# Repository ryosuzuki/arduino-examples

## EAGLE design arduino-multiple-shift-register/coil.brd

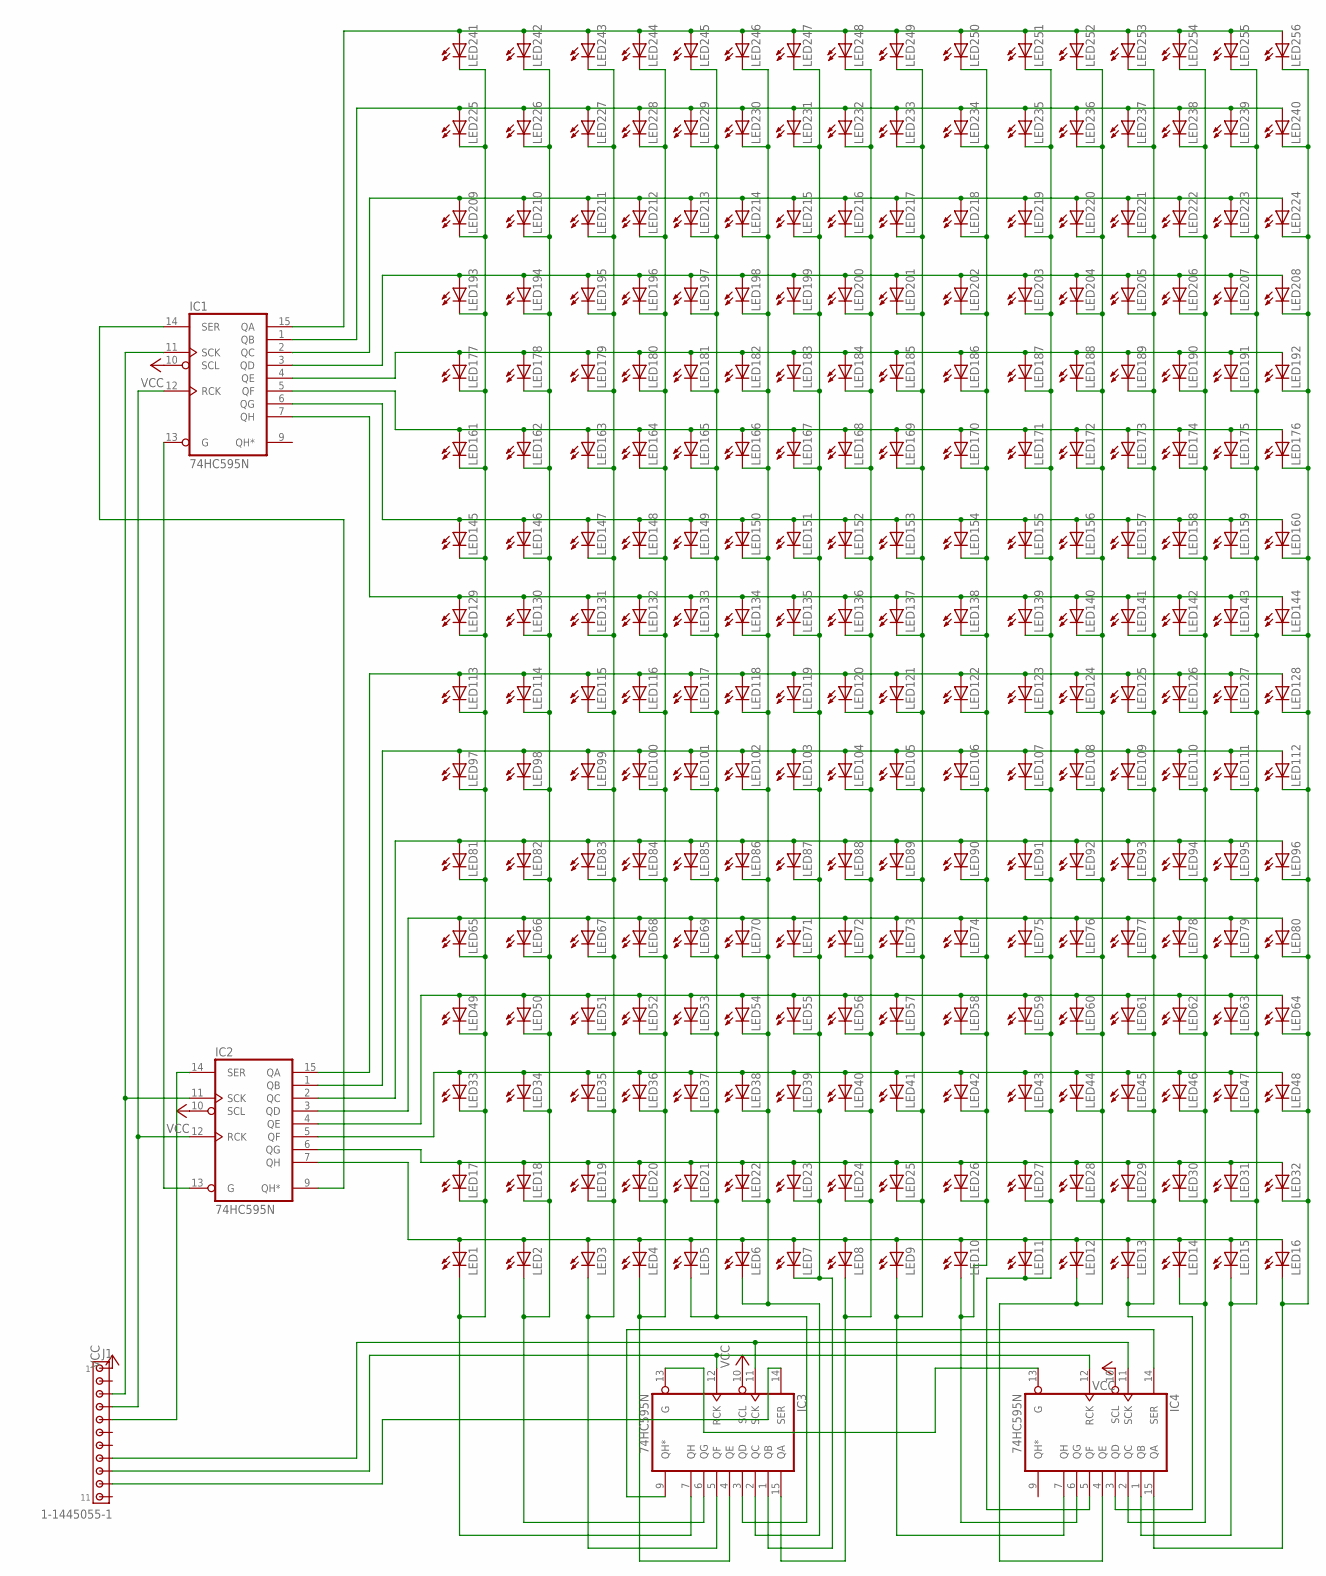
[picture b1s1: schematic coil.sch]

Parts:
IC1, IC2, IC3, IC4: 74HC595N; DIL16
J1: 1-1445055-1
LED1, LED2, LED3, LED4, LED5, LED6, LED7, LED8, LED9, LED10, LED11, LED12, LED13, LED14, LED15, LED16, LED17, LED18, LED19, LED20, LED21, LED22, LED23, LED24, LED25, LED26, LED27, LED28, LED29, LED30, LED31, LED32, LED33, LED34, LED35, LED36, LED37, LED38, LED39, LED40, LED41, LED42, LED43, LED44, LED45, LED46, LED47, LED48, LED49, LED50, LED51, LED52, LED53, LED54, LED55, LED56, LED57, LED58, LED59, LED60, LED61, LED62, LED63, LED64, LED65, LED66, LED67, LED68, LED69, LED70, LED71, LED72, LED73, LED74, LED75, LED76, LED77, LED78, LED79, LED80, LED81, LED82, LED83, LED84, LED85, LED86, LED87, LED88, LED89, LED90, LED91, LED92, LED93, LED94, LED95, LED96, LED97, LED98, LED99, LED100, LED101, LED102, LED103, LED104, LED105, LED106, LED107, LED108, LED109, LED110, LED111, LED112, LED113, LED114, LED115, LED116, LED117, LED118, LED119, LED120, LED121, LED122, LED123, LED124, LED125, LED126, LED127, LED128, LED129, LED130, LED131, LED132, LED133, LED134, LED135, LED136, LED137, LED138, LED139, LED140, LED141, LED142, LED143, LED144, LED145, LED146, LED147, LED148, LED149, LED150, LED151, LED152, LED153, LED154, LED155, LED156, LED157, LED158, LED159, LED160, LED161, LED162, LED163, LED164, LED165, LED166, LED167, LED168, LED169, LED170, LED171, LED172, LED173, LED174, LED175, LED176, LED177, LED178, LED179, LED180, LED181, LED182, LED183, LED184, LED185, LED186, LED187, LED188, LED189, LED190, LED191, LED192, LED193, LED194, LED195, LED196, LED197, LED198, LED199, LED200, LED201, LED202, LED203, LED204, LED205, LED206, LED207, LED208, LED209, LED210, LED211, LED212, LED213, LED214, LED215, LED216, LED217, LED218, LED219, LED220, LED221, LED222, LED223, LED224, LED225, LED226, LED227, LED228, LED229, LED230, LED231, LED232, LED233, LED234, LED235, LED236, LED237, LED238, LED239, LED240, LED241, LED242, LED243, LED244, LED245, LED246, LED247, LED248, LED249, LED250, LED251, LED252, LED253, LED254, LED255, LED256: LED5MM

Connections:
GND: IC1.8 (GND), IC2.8 (GND), IC3.8 (GND), IC4.8 (GND)
unnamed: IC2.7 (QH), LED1.A, LED2.A, LED3.A, LED4.A, LED5.A, LED6.A, LED7.A, LED8.A, LED9.A, LED10.A, LED11.A, LED12.A, LED13.A, LED14.A, LED15.A, LED16.A
unnamed: IC2.6 (QG), LED17.A, LED18.A, LED19.A, LED20.A, LED21.A, LED22.A, LED23.A, LED24.A, LED25.A, LED26.A, LED27.A, LED28.A, LED29.A, LED30.A, LED31.A, LED32.A
unnamed: IC2.5 (QF), LED33.A, LED34.A, LED35.A, LED36.A, LED37.A, LED38.A, LED39.A, LED40.A, LED41.A, LED42.A, LED43.A, LED44.A, LED45.A, LED46.A, LED47.A, LED48.A
unnamed: IC2.4 (QE), LED49.A, LED50.A, LED51.A, LED52.A, LED53.A, LED54.A, LED55.A, LED56.A, LED57.A, LED58.A, LED59.A, LED60.A, LED61.A, LED62.A, LED63.A, LED64.A
unnamed: IC2.3 (QD), LED65.A, LED66.A, LED67.A, LED68.A, LED69.A, LED70.A, LED71.A, LED72.A, LED73.A, LED74.A, LED75.A, LED76.A, LED77.A, LED78.A, LED79.A, LED80.A
unnamed: IC2.2 (QC), LED81.A, LED82.A, LED83.A, LED84.A, LED85.A, LED86.A, LED87.A, LED88.A, LED89.A, LED90.A, LED91.A, LED92.A, LED93.A, LED94.A, LED95.A, LED96.A
unnamed: IC2.1 (QB), LED97.A, LED98.A, LED99.A, LED100.A, LED101.A, LED102.A, LED103.A, LED104.A, LED105.A, LED106.A, LED107.A, LED108.A, LED109.A, LED110.A, LED111.A, LED112.A
unnamed: IC2.15 (QA), LED113.A, LED114.A, LED115.A, LED116.A, LED117.A, LED118.A, LED119.A, LED120.A, LED121.A, LED122.A, LED123.A, LED124.A, LED125.A, LED126.A, LED127.A, LED128.A
unnamed: IC1.7 (QH), LED129.A, LED130.A, LED131.A, LED132.A, LED133.A, LED134.A, LED135.A, LED136.A, LED137.A, LED138.A, LED139.A, LED140.A, LED141.A, LED142.A, LED143.A, LED144.A
unnamed: IC1.6 (QG), LED145.A, LED146.A, LED147.A, LED148.A, LED149.A, LED150.A, LED151.A, LED152.A, LED153.A, LED154.A, LED155.A, LED156.A, LED157.A, LED158.A, LED159.A, LED160.A
unnamed: IC1.5 (QF), LED161.A, LED162.A, LED163.A, LED164.A, LED165.A, LED166.A, LED167.A, LED168.A, LED169.A, LED170.A, LED171.A, LED172.A, LED173.A, LED174.A, LED175.A, LED176.A
unnamed: IC1.4 (QE), LED177.A, LED178.A, LED179.A, LED180.A, LED181.A, LED182.A, LED183.A, LED184.A, LED185.A, LED186.A, LED187.A, LED188.A, LED189.A, LED190.A, LED191.A, LED192.A
unnamed: IC1.3 (QD), LED193.A, LED194.A, LED195.A, LED196.A, LED197.A, LED198.A, LED199.A, LED200.A, LED201.A, LED202.A, LED203.A, LED204.A, LED205.A, LED206.A, LED207.A, LED208.A
unnamed: IC1.2 (QC), LED209.A, LED210.A, LED211.A, LED212.A, LED213.A, LED214.A, LED215.A, LED216.A, LED217.A, LED218.A, LED219.A, LED220.A, LED221.A, LED222.A, LED223.A, LED224.A
unnamed: IC1.1 (QB), LED225.A, LED226.A, LED227.A, LED228.A, LED229.A, LED230.A, LED231.A, LED232.A, LED233.A, LED234.A, LED235.A, LED236.A, LED237.A, LED238.A, LED239.A, LED240.A
unnamed: IC1.15 (QA), LED241.A, LED242.A, LED243.A, LED244.A, LED245.A, LED246.A, LED247.A, LED248.A, LED249.A, LED250.A, LED251.A, LED252.A, LED253.A, LED254.A, LED255.A, LED256.A
unnamed: IC4.3 (QD), LED13.K (C), LED29.K (C), LED45.K (C), LED61.K (C), LED77.K (C), LED93.K (C), LED109.K (C), LED125.K (C), LED141.K (C), LED157.K (C), LED173.K (C), LED189.K (C), LED205.K (C), LED221.K (C), LED237.K (C), LED253.K (C)
unnamed: IC4.2 (QC), LED14.K (C), LED30.K (C), LED46.K (C), LED62.K (C), LED78.K (C), LED94.K (C), LED110.K (C), LED126.K (C), LED142.K (C), LED158.K (C), LED174.K (C), LED190.K (C), LED206.K (C), LED222.K (C), LED238.K (C), LED254.K (C)
unnamed: IC4.1 (QB), LED15.K (C), LED31.K (C), LED47.K (C), LED63.K (C), LED79.K (C), LED95.K (C), LED111.K (C), LED127.K (C), LED143.K (C), LED159.K (C), LED175.K (C), LED191.K (C), LED207.K (C), LED223.K (C), LED239.K (C), LED255.K (C)
unnamed: IC3.7 (QH), LED1.K (C), LED17.K (C), LED33.K (C), LED49.K (C), LED65.K (C), LED81.K (C), LED97.K (C), LED113.K (C), LED129.K (C), LED145.K (C), LED161.K (C), LED177.K (C), LED193.K (C), LED209.K (C), LED225.K (C), LED241.K (C)
unnamed: IC3.6 (QG), LED2.K (C), LED18.K (C), LED34.K (C), LED50.K (C), LED66.K (C), LED82.K (C), LED98.K (C), LED114.K (C), LED130.K (C), LED146.K (C), LED162.K (C), LED178.K (C), LED194.K (C), LED210.K (C), LED226.K (C), LED242.K (C)
unnamed: IC3.5 (QF), LED3.K (C), LED19.K (C), LED35.K (C), LED51.K (C), LED67.K (C), LED83.K (C), LED99.K (C), LED115.K (C), LED131.K (C), LED147.K (C), LED163.K (C), LED179.K (C), LED195.K (C), LED211.K (C), LED227.K (C), LED243.K (C)
unnamed: IC3.4 (QE), LED4.K (C), LED20.K (C), LED36.K (C), LED52.K (C), LED68.K (C), LED84.K (C), LED100.K (C), LED116.K (C), LED132.K (C), LED148.K (C), LED164.K (C), LED180.K (C), LED196.K (C), LED212.K (C), LED228.K (C), LED244.K (C)
unnamed: IC3.3 (QD), LED5.K (C), LED21.K (C), LED37.K (C), LED53.K (C), LED69.K (C), LED85.K (C), LED101.K (C), LED117.K (C), LED133.K (C), LED149.K (C), LED165.K (C), LED181.K (C), LED197.K (C), LED213.K (C), LED229.K (C), LED245.K (C)
unnamed: IC3.2 (QC), LED6.K (C), LED22.K (C), LED38.K (C), LED54.K (C), LED70.K (C), LED86.K (C), LED102.K (C), LED118.K (C), LED134.K (C), LED150.K (C), LED166.K (C), LED182.K (C), LED198.K (C), LED214.K (C), LED230.K (C), LED246.K (C)
unnamed: IC3.1 (QB), LED7.K (C), LED23.K (C), LED39.K (C), LED55.K (C), LED71.K (C), LED87.K (C), LED103.K (C), LED119.K (C), LED135.K (C), LED151.K (C), LED167.K (C), LED183.K (C), LED199.K (C), LED215.K (C), LED231.K (C), LED247.K (C)
unnamed: IC3.15 (QA), LED8.K (C), LED24.K (C), LED40.K (C), LED56.K (C), LED72.K (C), LED88.K (C), LED104.K (C), LED120.K (C), LED136.K (C), LED152.K (C), LED168.K (C), LED184.K (C), LED200.K (C), LED216.K (C), LED232.K (C), LED248.K (C)
unnamed: IC4.7 (QH), LED9.K (C), LED25.K (C), LED41.K (C), LED57.K (C), LED73.K (C), LED89.K (C), LED105.K (C), LED121.K (C), LED137.K (C), LED153.K (C), LED169.K (C), LED185.K (C), LED201.K (C), LED217.K (C), LED233.K (C), LED249.K (C)
unnamed: IC4.6 (QG), LED10.K (C), LED26.K (C), LED42.K (C), LED58.K (C), LED74.K (C), LED90.K (C), LED106.K (C), LED122.K (C), LED138.K (C), LED154.K (C), LED170.K (C), LED186.K (C), LED202.K (C), LED218.K (C), LED234.K (C), LED250.K (C)
unnamed: IC4.5 (QF), LED11.K (C), LED27.K (C), LED43.K (C), LED59.K (C), LED75.K (C), LED91.K (C), LED107.K (C), LED123.K (C), LED139.K (C), LED155.K (C), LED171.K (C), LED187.K (C), LED203.K (C), LED219.K (C), LED235.K (C), LED251.K (C)
unnamed: IC4.4 (QE), LED12.K (C), LED28.K (C), LED44.K (C), LED60.K (C), LED76.K (C), LED92.K (C), LED108.K (C), LED124.K (C), LED140.K (C), LED156.K (C), LED172.K (C), LED188.K (C), LED204.K (C), LED220.K (C), LED236.K (C), LED252.K (C)
unnamed: IC4.15 (QA), LED16.K (C), LED32.K (C), LED48.K (C), LED64.K (C), LED80.K (C), LED96.K (C), LED112.K (C), LED128.K (C), LED144.K (C), LED160.K (C), LED176.K (C), LED192.K (C), LED208.K (C), LED224.K (C), LED240.K (C), LED256.K (C)
unnamed: IC3.11 (SCK), IC4.11 (SCK), J1.8
unnamed: IC3.12 (RCK), IC4.12 (RCK), J1.9
unnamed: IC3.9 (QH*), IC4.14 (SER)
unnamed: IC3.13 (G), IC4.13 (G)
unnamed: IC1.14 (SER), IC2.9 (QH*)
unnamed: IC1.11 (SCK), IC2.11 (SCK), J1.3
unnamed: IC1.12 (RCK), IC2.12 (RCK), J1.4
unnamed: IC1.13 (G), IC2.13 (G)
unnamed: IC2.14 (SER), J1.5
unnamed: IC3.14 (SER), J1.10
VCC: IC1.10 (SCL), IC1.16 (VCC), IC2.10 (SCL), IC2.16 (VCC), IC3.10 (SCL), IC3.16 (VCC), IC4.10 (SCL), IC4.16 (VCC), J1.1

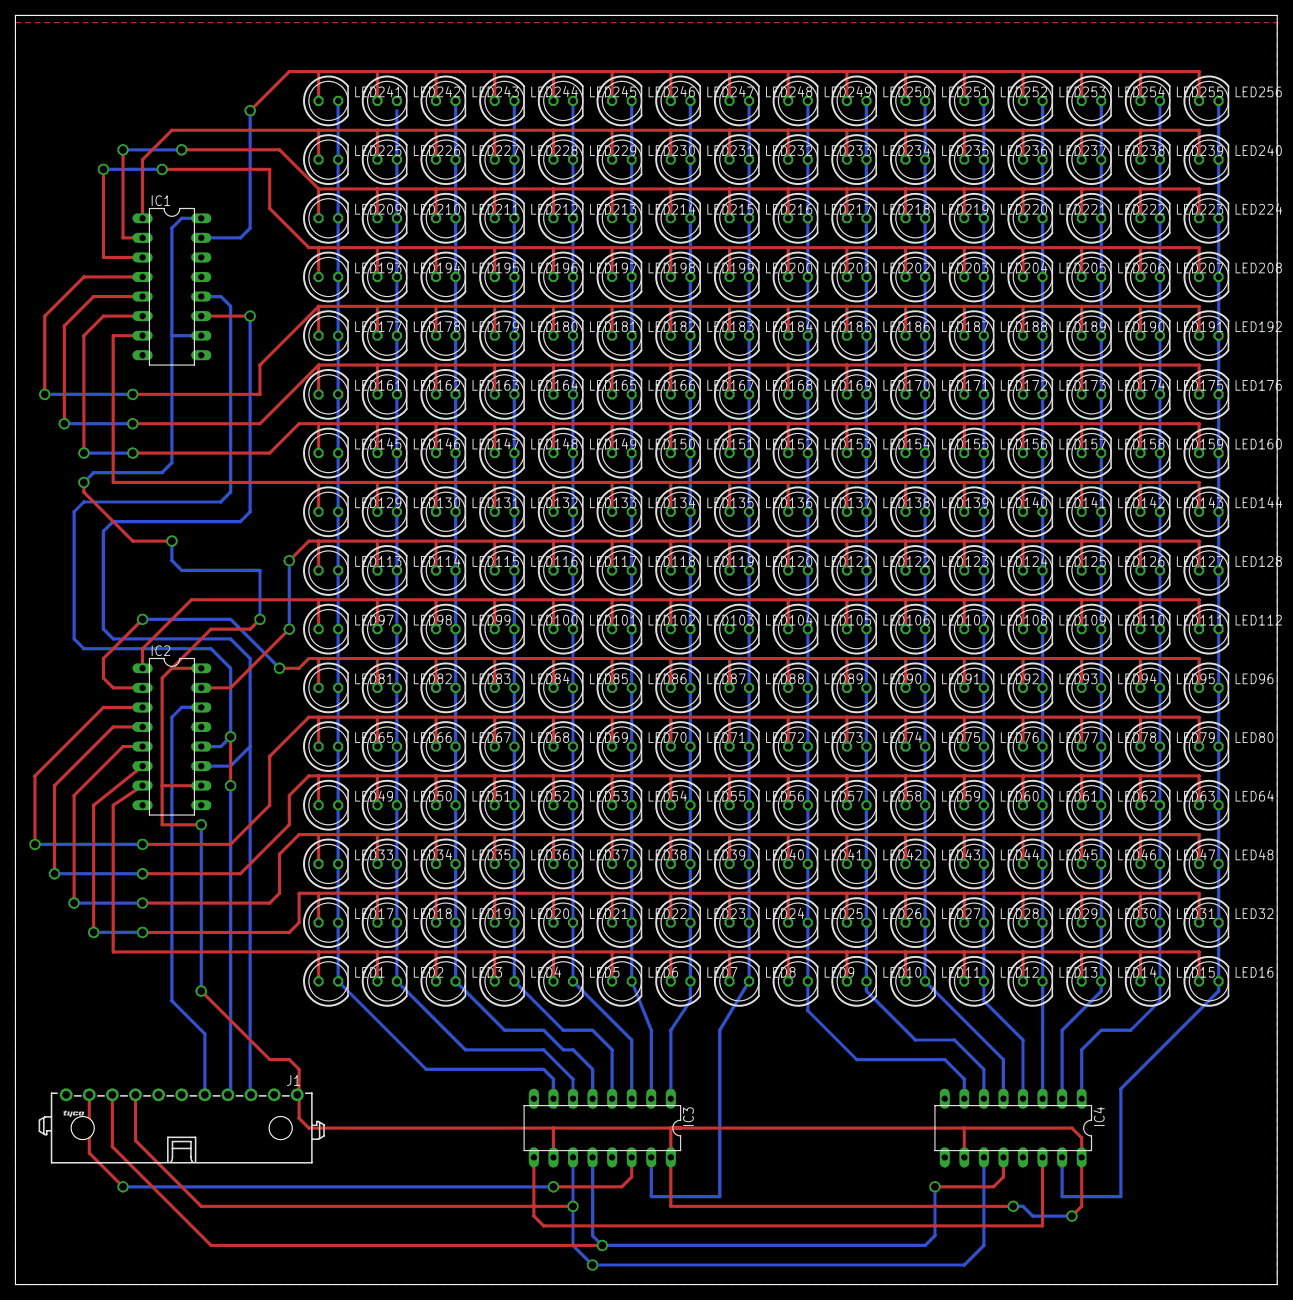
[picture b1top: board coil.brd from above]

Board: 2 copper layers, 163.8 x 164.8 mm, 261 parts (0 on the bottom side), 44 nets.

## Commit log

2016-11-06 Add bluetooth led blink
2016-11-06 Correct fritzing image
2016-11-06 Add motor control
2016-11-08 Add ESP8266 and ESP32 examples
2016-11-09 Update name
2016-11-09 Add fritzing for ESP8266 motor control
2016-11-09 Add web-motor-control
2016-11-09 Add web control interface
2016-11-09 Use APIP instead of wi-fi
2017-02-24 Add shift register
2017-03-06 Add esp 8266 shift register
2017-03-12 Add esp8266-micro-coil
2017-06-05 Add attiny85 led blink
2017-06-06 Add Attiny one wire and i2c communication
2017-06-06 Add attiny i2c slave arduino moster communcation
2017-06-06 Enable to control Attiny slave from Arduino master
2017-06-06 Add fritzing schematic
2017-07-07 Add arduino servo motor examples
2017-07-09 Add Arduino coil pwm experiment
2017-07-13 Add arduino coil shift regiester with pwm traveling
2017-07-13 Add package.json
2017-07-13 Add serial.js for multiple shift registers
2017-07-13 Add LED Matrix board layout
2017-07-24 Add accel stepper
2017-07-27 Add multipe stepper
